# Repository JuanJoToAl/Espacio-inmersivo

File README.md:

# Documentacion Espacio Inmersivo

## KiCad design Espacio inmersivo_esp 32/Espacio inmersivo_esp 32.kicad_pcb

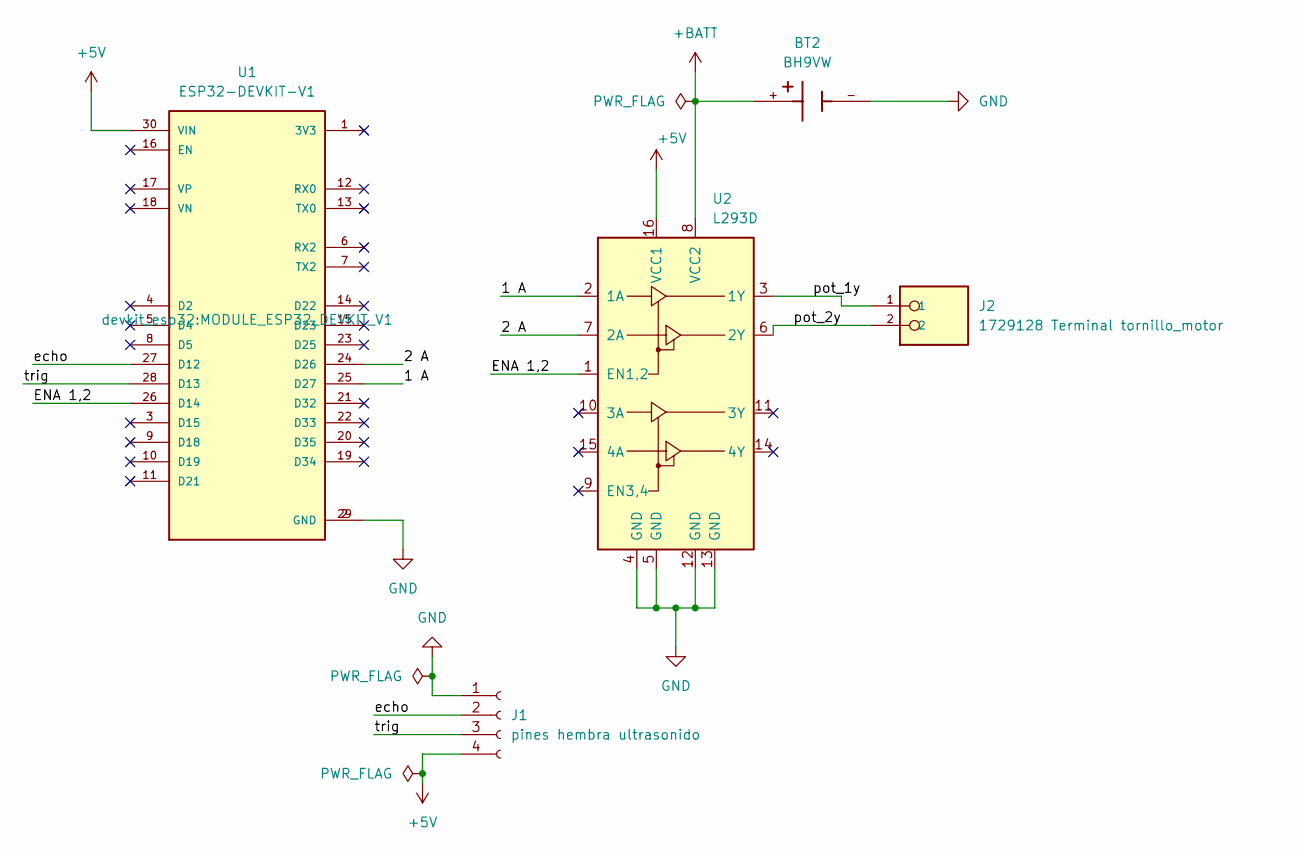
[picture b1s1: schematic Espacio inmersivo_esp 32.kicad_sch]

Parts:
BT2: BH9VW; BAT_BH9VW; PARTREV D
J1: pines hembra ultrasonido; PinSocket_1x04_P2.54mm_Vertical
J2: 1729128 Terminal tornillo_motor; PHOENIX_1729128; PARTREV 28.07.2023
U1: ESP32-DEVKIT-V1; MODULE_ESP32_DEVKIT_V1; PARTREV N/A
U2: L293D; DIP-16_W7.62mm

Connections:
+5V: J1.4, U1.30 (VIN), U2.16 (VCC1)
+BATT: BT2.+, U2.8 (VCC2)
/1 A: U1.25 (D27), U2.2 (1A)
/2 A: U1.24 (D26), U2.7 (2A)
/ENA 1,2: U1.26 (D14), U2.1 (EN1,2)
/echo: J1.2, U1.27 (D12)
/pot_1y: J2.1, U2.3 (1Y)
/pot_2y: J2.2, U2.6 (2Y)
/trig: J1.3, U1.28 (D13)
GND: BT2.-, J1.1, U1.2 (GND), U1.29 (GND), U2.4 (GND), U2.5 (GND), U2.12 (GND), U2.13 (GND)

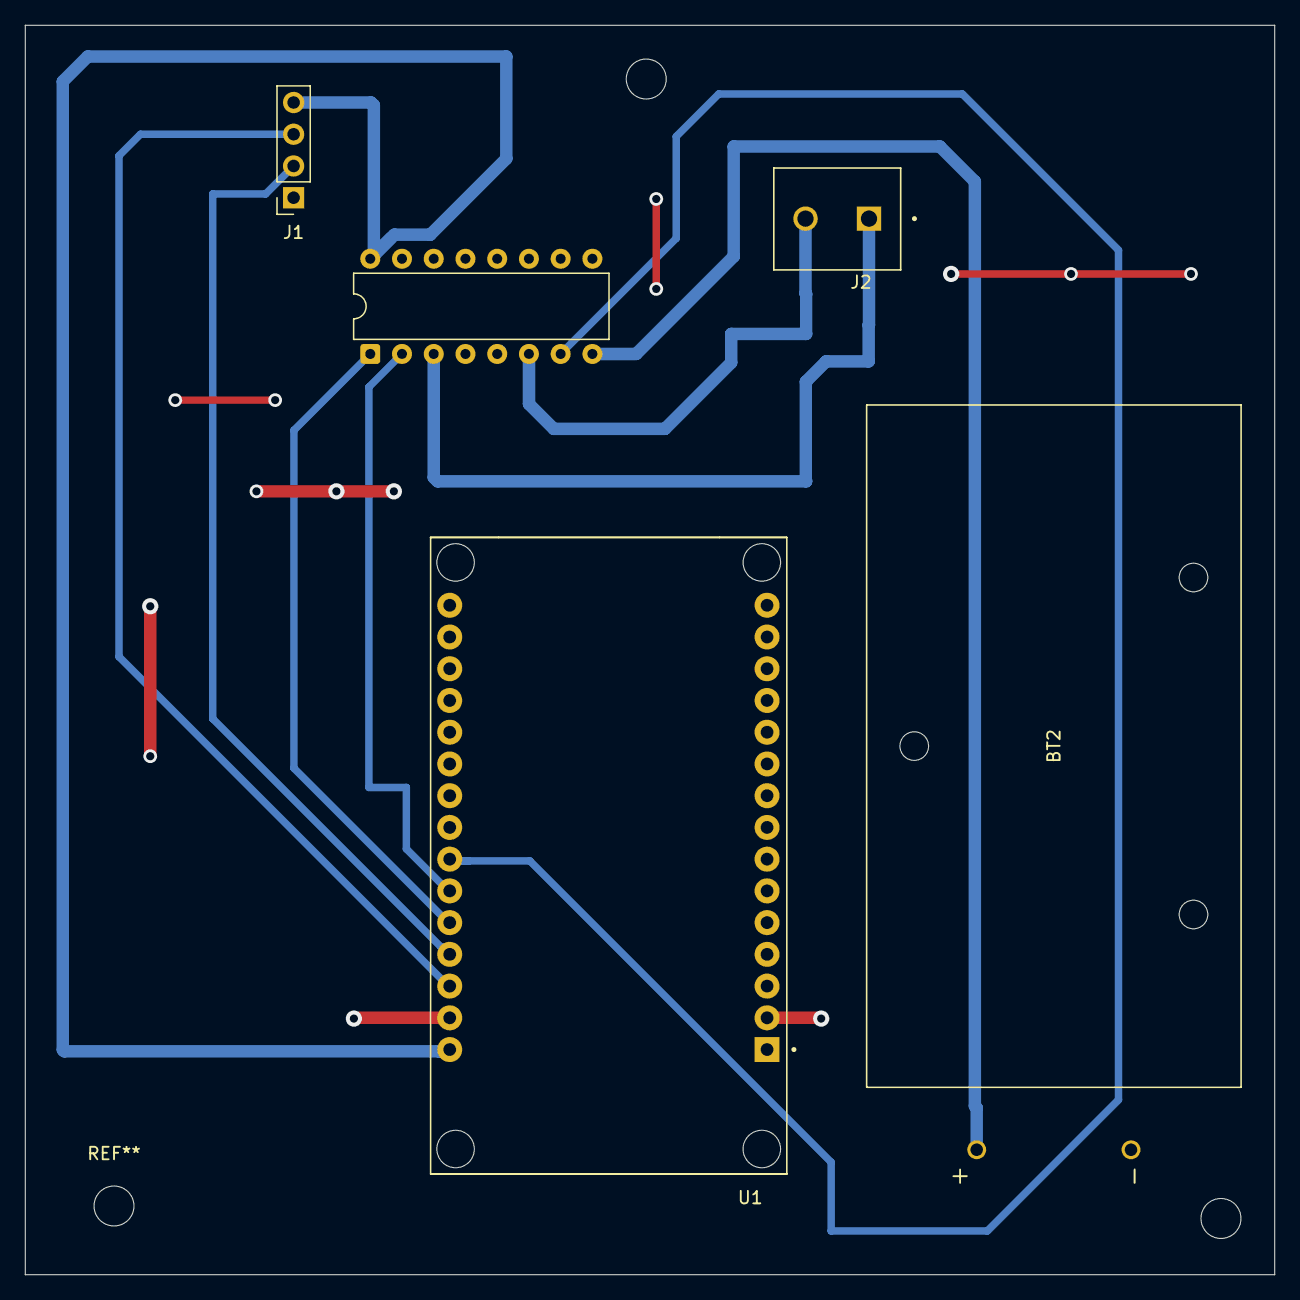
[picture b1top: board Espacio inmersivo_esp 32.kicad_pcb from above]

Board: 2 copper layers, 100.0 x 100.0 mm, 5 parts (0 on the bottom side), 10 nets.

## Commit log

2025-02-27 Create Espacio inmersivo
2025-02-27 Rename Espacio inmersivo to Documentación
2025-03-05 Rename Tablero virtual de lluvia de ideas sobre el proceso de ventas.png to Diagrama de caja negra .png
2025-03-05 Rename Diagrama de caja negra .png to Diagrama de caja negra.png
2025-03-05 Rename Tablero virtual de lluvia de ideas sobre el proceso de ventas (1).png to Diagrama de flujo general del proyecto.png
2025-03-05 Rename 38 cm (1)_page-0001.jpg to Diseño para corte láser.jpg
2025-03-05 Rename WhatsApp Image 2025-01-21 at 6.54.32 PM.jpeg to Modelo reducido de estructura MDF.jpeg
2025-03-05 Rename 3.png to Diagrama de flujo código.png
2025-03-07 Rename whatsapp-video-2025-01-28-at-63156-pm_6CUoUSz8.mp4 to versión en miniatura del espacio inmersivo.mp4
2025-03-07 Rename IMG-20250307-WA0027.jpg to PCB con componentes integrados.jpg
